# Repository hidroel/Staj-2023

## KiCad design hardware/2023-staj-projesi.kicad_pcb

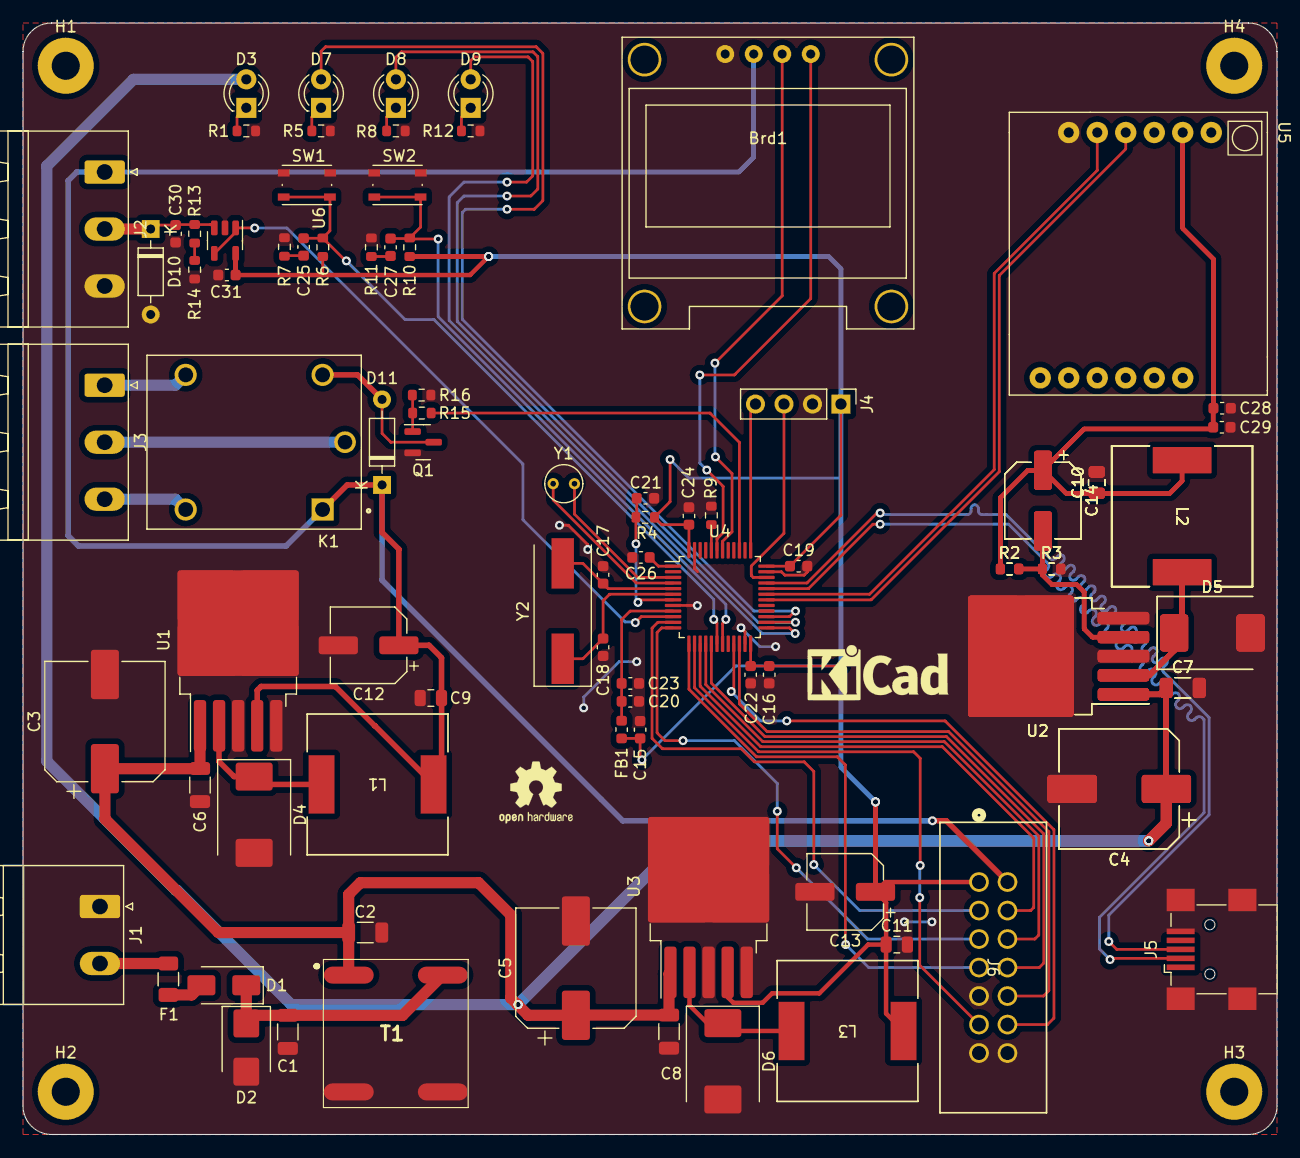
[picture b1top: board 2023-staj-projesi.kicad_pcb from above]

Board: 2 copper layers, 111.8 x 99.1 mm, 96 parts (0 on the bottom side), 57 nets.

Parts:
Brd1: SSD1306; SSD1306_0.96_Oled
C1, C2: CL31B104KBCNFNC; C_1206_3216Metric
C3, C4, C4#2, C5: 100uF/63V; CP_Elec_10x10.5
C6, C7, C7#2, C8: 470nF/100V; C_1206_3216Metric
C9, C10, C10#2, C11: 100nF/20V; C_0805_2012Metric
C12, C13, C14, C14#2: 100uF/20V; CP_Elec_6.3x7.7
C15, C20, C28: 1uF; C_0603_1608Metric
C16: 10uF; C_0603_1608Metric
C17, C18: 20pF; C_0603_1608Metric
C19, C21, C22, C24, C25, C27, C29, C31: 100nF; C_0603_1608Metric
C23, C30: 10nF; C_0603_1608Metric
C26: 1uF/10V; C_0603_1608Metric
D1: SBR3A40SAQ; D_SMA
D2: SMBJ28A; D_SMB
D3: LED_PWR; LED_D3.0mm
D4, D5, D5#2, D6: SK56; D_SMC
D7: LED_ACT; LED_D3.0mm
D8: LED_DEACT; LED_D3.0mm
D9: LED_ERR; LED_D3.0mm
D10: SMBJ28A; D_DO-35_SOD27_P7.62mm_Horizontal
D11: 1N4148; D_DO-35_SOD27_P7.62mm_Horizontal
F1: Fuse; Fuse_1206_3216Metric
FB1: 120R; L_0603_1608Metric
H1, H2, H3, H4: MountingHole; MountingHole_2.5mm_Pad
J1: POWER; PhoenixContact_MSTBA_2,5_2-G-5,08_1x02_P5.08mm_Horizontal
J2: SENSOR; PhoenixContact_MSTBA_2,5_3-G-5,08_1x03_P5.08mm_Horizontal
J3: RELAY; PhoenixContact_MSTBA_2,5_3-G-5,08_1x03_P5.08mm_Horizontal
J4: SW; PinHeader_1x04_P2.54mm_Vertical
J5: USB_B_Mini; USB_Mini-B_Wuerth_65100516121_Horizontal
J6: EXT; CONN14_1421621_WRE
K1: SRD-05VDC-SL-C; RELAY_SRD-05VDC-SL-C
L1, L2, L2#2, L3: 74477020; IND_1280-WE-PD_WRE
Q1: BC847; SOT-23
R1: 1K2; R_0603_1608Metric
R2, R2#2: 2K2; R_0603_1608Metric
R3, R3#2: 1K; R_0603_1608Metric
R4: 10K; R_0603_1608Metric
R5, R8, R12: 470R; R_0603_1608Metric
R6, R10, R15: 4K7; R_0603_1608Metric
R7, R11: 100R; R_0603_1608Metric
R9: 100K; R_0603_1608Metric
R13: 150R; R_0603_1608Metric
R14: 15R; R_0603_1608Metric
R16: 47K; R_0603_1608Metric
SW1: BTN_ACT; SW_Push_1P1T_NO_Vertical_Wuerth_434133025816
SW2: BTN_DEACT; SW_Push_1P1T_NO_Vertical_Wuerth_434133025816
T1: PA2748NL
U1: LM2596S-5; TO-263-5_TabPin3
U2, U2#2: LM2596S-ADJ; TO-263-5_TabPin3
U3: LM2596S-3.3; TO-263-5_TabPin3
U4: STM32F103C8T6; LQFP-48_7x7mm_P0.5mm
U5: SIM800L-CORE
U6: AD8603; TSOT-23-5
Y1: 32KHz; Crystal_C38-LF_D3.0mm_L8.0mm_Vertical
Y2: 8MHz; Crystal_SMD_HC49-SD

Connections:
+3.3VA: C20.1, C23.1, FB1.2, U4.9 (VDDA)
+3V3: C11.1, C13.1, C15.1, C16.1, C19.1, C22.1, C24.1, C31.1, FB1.1, J4.1, J6.1, L3.1, R4.2, R6.1, R10.1, U3.4 (FB), U4.24 (VDD), U4.36 (VDD), U4.48 (VDD), U6.5 (V+)
+3V8: C10.1, C10#2.1, C14.1, C14#2.1, C28.1, C29.1, L2.1, L2#2.1, R2.1, R2#2.1, U5.2 (VCC)
+5V: Brd1.2 (VCC), C9.1, C12.1, D11.1 (K), J2.1, J6.2, K1.A1, L1.1, U1.4 (FB)
/ADC/ADC: U4.10 (PA0), U6.1, U6.4 (-)
/ADC/SENSOR: C30.1, D10.1 (K), J2.2, R13.1, U6.3 (+)
/GSM/RXD: U4.30 (PA9), U5.4 (RXD)
/GSM/TXD: U4.31 (PA10), U5.5 (TXD)
/LCD/SCL: Brd1.3 (SCL), U4.42 (PB6)
/LCD/SDA: Brd1.4 (SDA), U4.43 (PB7)
/MCU/BOOT: R9.1, U4.44 (BOOT0)
/MCU/BTN_ACT: C25.1, R6.2, SW1.2, U4.18 (PB0)
/MCU/BTN_DEACT: C27.1, R10.2, SW2.2, U4.19 (PB1)
/MCU/I2C2_SCL: J6.12, U4.21 (PB10)
/MCU/I2C2_SDA: J6.10, U4.22 (PB11)
/MCU/LED_ACT: D7.2 (A), U4.27 (PB14)
/MCU/LED_DEACT: D8.2 (A), U4.26 (PB13)
/MCU/LED_ERR: D9.2 (A), U4.25 (PB12)
/MCU/NRST: C21.1, R4.1, U4.7 (NRST)
/MCU/PA1: J6.3, U4.11 (PA1)
/MCU/PA4: J6.11, U4.14 (PA4)
/MCU/RCC_OSC32_IN: U4.3 (PC14), Y1.2
/MCU/RCC_OSC32_OUT: U4.4 (PC15), Y1.1
/MCU/RCC_OSC_IN: C17.2, U4.5 (PD0), Y2.2
/MCU/RCC_OSC_OUT: C18.2, U4.6 (PD1), Y2.1
/MCU/RELAY: R15.1, U4.39 (PB3)
/MCU/SPI1_MISO: J6.6, U4.16 (PA6)
/MCU/SPI1_MOSI: J6.8, U4.17 (PA7)
/MCU/SPI1_SCK: J6.4, U4.15 (PA5)
/MCU/SWCLK: J4.4, U4.37 (PA14)
/MCU/SWDIO: J4.3, U4.34 (PA13)
/MCU/USART2_RX: J6.7, U4.13 (PA3)
/MCU/USART2_TX: J6.5, U4.12 (PA2)
/MCU/USB_D+: J5.3 (D+), U4.33 (PA12)
/MCU/USB_D-: J5.2 (D-), U4.32 (PA11)
/MCU/VBAT: C26.1, U4.1 (VBAT)
/Power/+12V: C2.1, C3.1, C4.1, C4#2.1, C5.1, C6.1, C7.1, C7#2.1, C8.1, D3.2 (A), T1.1 (PRI_1), U1.1 (VIN), U2.1 (VIN), U2#2.1 (VIN), U3.1 (VIN)
/Power/VCC: F1.1, J1.2
/RELAY/RLIN: J3.2, K1.COM
/RELAY/RLNC: J3.3, K1.NC
/RELAY/RLNO: J3.1, K1.NO
GND: Brd1.1 (GND), C1.2, C2.2, C3.2, C4.2, C4#2.2, C5.2, C6.2, C7.2, C7#2.2, C8.2, C9.2, C10.2, C10#2.2, C11.2, C12.2, C13.2, C15.2, C16.2, C17.1, C18.1, C19.2, C20.2, C21.2, C22.2, C23.2, C24.2, C26.2, C28.2, C29.2, C30.2, C31.2, D2.2 (A), D4.2 (A), D5.2 (A), D5#2.2 (A), D6.2 (A), D10.2 (A), J1.1, J2.3, J4.2, J5.5 (GND), J5.6 (Shield), J6.9, J6.13, J6.14, Q1.2 (E), R1.2, R3.2, R3#2.2, R5.2, R7.2, R8.2, R9.2, R11.2, R12.2, R14.2, R16.2, SW1.1, SW2.1, T1.2 (PRI_2), T1.4 (SEC_2), U1.3 (GND), U1.5 (~ON/OFF), U2.3 (GND), U2.5 (~ON/OFF), U2#2.3 (GND), U2#2.5 (~ON/OFF), U3.3 (GND), U3.5 (~ON/OFF), U4.8 (VSSA), U4.23 (VSS), U4.35 (VSS), U4.47 (VSS), U5.6 (GND), U6.2 (V-)
unnamed: C25.2, R7.1
unnamed: C27.2, R11.1
unnamed: D1.2 (A), F1.2
unnamed: C1.1, D1.1 (K), D2.1 (K), T1.3 (SEC_1)
unnamed: D3.1 (K), R1.1
unnamed: D4.1 (K), L1.2, U1.2 (OUT)
unnamed: D5.1 (K), D5#2.1 (K), L2.2, L2#2.2, U2.2 (OUT), U2#2.2 (OUT)
unnamed: D6.1 (K), L3.2, U3.2 (OUT)
unnamed: D7.1 (K), R5.1
unnamed: D8.1 (K), R8.1
unnamed: D9.1 (K), R12.1
unnamed: D11.2 (A), K1.A2, Q1.3 (C)
unnamed: Q1.1 (B), R15.2, R16.1
unnamed: R13.2, R14.1
unnamed: C14.2, C14#2.2, R2.2, R2#2.2, R3.1, R3#2.1, U2.4 (FB), U2#2.4 (FB)

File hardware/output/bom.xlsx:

Item | Qty | Reference(s) | Value | LibPart | Footprint | Datasheet | DNP | Arrow Part Number | Arrow Price/Stock | Digikey | DigikeyPN | Height | MANUFACTURER | Manufacturer_Name | Manufacturer_Part_Number | Mouser Part Number | Mouser Price/Stock | STANDARD | Sim.Device | Sim.Pins
1 | 1 | Brd1 | SSD1306 | 2023Staj:SSD1306 | 2023Staj:SSD1306_0.96_Oled
2 | 2 | C1, C2 | CL31B104KBCNFNC | Device:C_Small | Capacitor_SMD:C_1206_3216Metric | ~ |  |  |  |  | 1276-2744-2-ND
3 | 3 | C3, C4, C5 | 100uF/63V | Device:C_Polarized | Capacitor_SMD:CP_Elec_10x10.5 | ~ |  |  |  |  | 399-15648-6-ND
4 | 3 | C6, C7, C8 | 470nF/100V | Device:C_Small | Capacitor_SMD:C_1206_3216Metric | ~ |  |  |  |  | 399-C1206C474M1REC7210DKR-ND
5 | 3 | C9, C10, C11 | 100nF/20V | Device:C_Small | Capacitor_SMD:C_0805_2012Metric | ~ |  |  |  |  | 718-2500-6-ND
6 | 3 | C12, C13, C14 | 100uF/20V | Device:C_Polarized | Capacitor_SMD:CP_Elec_6.3x7.7 | ~ |  |  |  |  | 565-3210-6-ND
7 | 2 | C15, C20 | 1uF | Device:C_Small | Capacitor_SMD:C_0603_1608Metric | ~ |  |  |  |  | 311-1447-6-ND
8 | 1 | C16 | 10uF | Device:C_Small | Capacitor_SMD:C_0603_1608Metric | ~ |  |  |  |  | 13-CC0603MPX5R5BB106DKR-ND
9 | 2 | C17, C18 | 20pF | Device:C_Small | Capacitor_SMD:C_0603_1608Metric | ~ |  |  |  |  | 399-C0603C200G8HAC7867DKR-ND
10 | 6 | C19, C21, C22, C24, C25, C27 | 100nF | Device:C_Small | Capacitor_SMD:C_0603_1608Metric | ~ |  |  |  |  | AC0603KPX7R7BB104
11 | 1 | C23 | 10nF | Device:C_Small | Capacitor_SMD:C_0603_1608Metric | ~ |  |  |  |  | 13-CC0100KRX5R4BB103TR-ND
12 | 1 | C26 | 1uF/10V | Device:CP | Capacitor_SMD:C_0603_1608Metric |  |  |  |  |  | 478-12231-6-ND
13 | 1 | C28 | 1uF | Device:C | Capacitor_SMD:C_0603_1608Metric | ~
14 | 2 | C29, C31 | 100nF | Device:C | Capacitor_SMD:C_0603_1608Metric | ~
15 | 1 | C30 | 10nF | Device:C | Capacitor_SMD:C_0603_1608Metric | ~
16 | 1 | D1 | SBR3A40SAQ | Device:D | Diode_SMD:D_SMA | ~ |  |  |  |  | SBR3A40SAQ-13DITR-ND
17 | 1 | D2 | SMBJ28A | Device:D | Diode_SMD:D_SMB | ~ |  |  |  |  | SMBJ28ALFDKR-ND
18 | 1 | D3 | LED_PWR | Device:LED_Small | LED_THT:LED_D3.0mm | ~ |  |  |  |  | 1830-1004-ND
19 | 3 | D4, D5, D6 | SK56 | Device:D_Schottky | Diode_SMD:D_SMC | ~ |  |  |  |  | 1655-SK56DKR-ND
20 | 1 | D7 | LED_ACT | Device:LED_Small | LED_THT:LED_D3.0mm | ~ |  |  |  |  | 1830-1004-ND
21 | 1 | D8 | LED_DEACT | Device:LED_Small | LED_THT:LED_D3.0mm | ~ |  |  |  |  | 1830-1001-ND
22 | 1 | D9 | LED_ERR | Device:LED_Small | LED_THT:LED_D3.0mm | ~ |  |  |  |  | 1830-1000-ND
23 | 1 | D10 | SMBJ28A | Diode:1N914 | Diode_THT:D_DO-35_SOD27_P7.62mm_Horizontal | http://www.vishay.com/docs/85622/1n914.pdf |  |  |  |  |  |  |  |  |  |  |  |  | D | 1=K 2=A
24 | 1 | D11 | 1N4148 | Diode:1N4148 | Diode_THT:D_DO-35_SOD27_P7.62mm_Horizontal | https://assets.nexperia.com/documents/data-sheet/1N4148_1N4448.pdf |  |  |  |  |  |  |  |  |  |  |  |  | D | 1=K 2=A
25 | 1 | F1 | Fuse | Device:Fuse | Fuse:Fuse_1206_3216Metric | ~
26 | 1 | FB1 | 120R | Device:FerriteBead | Inductor_SMD:L_0603_1608Metric | ~ |  |  |  |  | 732-4665-6-ND
27 | 1 | J1 | POWER | Connector:Screw_Terminal_01x02 | Connector_Phoenix_MSTB:PhoenixContact_MSTBA_2,5_2-G-5,08_1x02_P5.08mm_Horizontal | ~
28 | 1 | J2 | SENSOR | Connector:Screw_Terminal_01x03 | Connector_Phoenix_MSTB:PhoenixContact_MSTBA_2,5_3-G-5,08_1x03_P5.08mm_Horizontal | ~
29 | 1 | J3 | RELAY | Connector:Screw_Terminal_01x03 | Connector_Phoenix_MSTB:PhoenixContact_MSTBA_2,5_3-G-5,08_1x03_P5.08mm_Horizontal | ~
30 | 1 | J5 | USB_B_Mini | Connector:USB_B_Mini | Connector_USB:USB_Mini-B_Wuerth_65100516121_Horizontal | ~ |  |  |  | 732-2109-2-ND
31 | 1 | J6 | EXT | Connector_Generic:Conn_02x07_Odd_Even | Connector_JAE:JAE_LY20-14P-DT1_2x07_P2.00mm_Vertical | ~
32 | 1 | K1 | SRD-05VDC-SL-C | 2023Staj:SRD-05VDC-SL-C | 2023Staj:RELAY_SRD-05VDC-SL-C |  |  |  |  |  |  |  | SONGLE RELAY |  |  |  |  | IPC-7251
33 | 3 | L1, L2, L3 | 74477020 | Damlama:74477020 | 2023Staj:IND_1280-WE-PD_WRE | 74477020 |  |  |  |  | 732-1235-6-ND
34 | 1 | Q1 | BC847 | Transistor_BJT:BC847 | Package_TO_SOT_SMD:SOT-23 | http://www.infineon.com/dgdl/Infineon-BC847SERIES_BC848SERIE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
35 | 1 | R1 | 1K2 | Device:R_Small | Resistor_SMD:R_0603_1608Metric | ~ |  |  |  |  | 13-RC0603FR-131K2LDKR-ND
36 | 1 | R2 | 2K2 | Device:R | Resistor_SMD:R_0603_1608Metric | ~
37 | 1 | R3 | 1K | Device:R | Resistor_SMD:R_0603_1608Metric | ~
38 | 1 | R4 | 10K | Device:R_Small | Resistor_SMD:R_0603_1608Metric | ~ |  |  |  |  | RNCP0603FTD10K0DKR-ND
39 | 3 | R5, R8, R12 | 470R | Device:R_Small | Resistor_SMD:R_0603_1608Metric | ~ |  |  |  |  | 1292-WR06X471JTLDKR-ND
40 | 3 | R6, R10, R15 | 4K7 | Device:R_Small | Resistor_SMD:R_0603_1608Metric | ~ |  |  |  |  | 13-RC1206FR-134K7LDKR-ND
41 | 2 | R7, R11 | 100R | Device:R_Small | Resistor_SMD:R_0603_1608Metric | ~ |  |  |  |  | RR08P100DDKR-ND
42 | 1 | R9 | 100K | Device:R | Resistor_SMD:R_0603_1608Metric | ~ |  |  |  | 311-100KHRDKR-ND
43 | 1 | R13 | 150R | Device:R | Resistor_SMD:R_0603_1608Metric | ~
44 | 1 | R14 | 15R | Device:R | Resistor_SMD:R_0603_1608Metric | ~
45 | 1 | R16 | 47K | Device:R_Small | Resistor_SMD:R_0603_1608Metric | ~
46 | 1 | SW1 | BTN_ACT | Switch:SW_Push | Button_Switch_SMD:SW_Push_1P1T_NO_Vertical_Wuerth_434133025816 | ~ |  |  |  |  | 732-13663-6-ND
47 | 1 | SW2 | BTN_DEACT | Switch:SW_Push | Button_Switch_SMD:SW_Push_1P1T_NO_Vertical_Wuerth_434133025816 | ~ |  |  |  |  | 732-13663-6-ND
48 | 1 | T1 | PA2748NL | Damlama:PA2748NL | Damlama:PA2748NL | https://productfinder.pulseelectronics.com/api/open/part-att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 |  | PA2748NL | https://www.arrow.com/en/products/pa2748nl/pulse-electronics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 |  | 553-2186-ND | 56 |  | Pulse | PA2748NL | 673-PA2748NL | https://www.mouser.co.uk/ProductDetail/Pulse-Electronics/PA2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
49 | 1 | U1 | LM2596S-5 | Regulator_Switching:LM2596S-5 | Package_TO_SOT_SMD:TO-263-5_TabPin3 | http://www.ti.com/lit/ds/symlink/lm2596.pdf |  |  |  |  | LM2596S-5.0-ND
50 | 1 | U2 | LM2596S-ADJ | Regulator_Switching:LM2596S-ADJ | Package_TO_SOT_SMD:TO-263-5_TabPin3 | http://www.ti.com/lit/ds/symlink/lm2596.pdf |  |  |  | 296-35399-2-ND
51 | 1 | U3 | LM2596S-3.3 | Regulator_Switching:LM2596S-3.3 | Package_TO_SOT_SMD:TO-263-5_TabPin3 | http://www.ti.com/lit/ds/symlink/lm2596.pdf |  |  |  |  | LM2596S-3.3/NOPB-ND
52 | 1 | U4 | STM32F103C8T6 | MCU_ST_STM32F1:STM32F103C8Tx | Package_QFP:LQFP-48_7x7mm_P0.5mm | https://www.st.com/resource/en/datasheet/stm32f103c8.pdf |  |  |  |  | 497-6063-ND
53 | 1 | U5 | SIM800L-CORE | 2023Staj:SIM800L-CORE | 2023Staj:SIM800L-CORE
54 | 1 | U6 | AD8603 | Amplifier_Operational:AD8603 | Package_TO_SOT_SMD:TSOT-23-5 | https://www.analog.com/media/en/technical-documentation/data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
55 | 1 | Y1 | 32KHz | Device:Crystal | Crystal:Crystal_C38-LF_D3.0mm_L8.0mm_Vertical | https://ecsxtal.com/store/pdf/ECS-3x8X%202x6X%201X5X.pdf |  |  |  |  | X1123-ND
56 | 1 | Y2 | 8MHz | Device:Crystal | Crystal:Crystal_SMD_HC49-SD | https://ecsxtal.com/store/pdf/ECS-3x8X%202x6X%201X5X.pdf |  |  |  |  | 631-1010-6-ND

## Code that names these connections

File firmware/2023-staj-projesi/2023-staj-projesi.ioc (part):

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Mcu.Name=STM32F103C(8-B)Tx
Mcu.Package=LQFP48
Mcu.UserName=STM32F103C8Tx
PA0-WKUP.Signal=ADCx_IN0
PA1.GPIOParameters=GPIO_Label
PA1.GPIO_Label=PA1
PA1.Signal=GPIO_Output
PA10.Mode=Asynchronous
PA10.Signal=USART1_RX
PA11.Mode=Device
PA11.Signal=USB_DM
PA12.Mode=Device
PA12.Signal=USB_DP
PA13.Mode=Serial_Wire
PA13.Signal=SYS_JTMS-SWDIO
PA14.Mode=Serial_Wire
PA14.Signal=SYS_JTCK-SWCLK
PA2.Mode=Asynchronous
PA2.Signal=USART2_TX
PA3.Mode=Asynchronous
PA3.Signal=USART2_RX
PA4.GPIOParameters=GPIO_Label
PA4.GPIO_Label=PA4
PA4.Signal=GPIO_Output
PA5.Mode=Full_Duplex_Master
PA5.Signal=SPI1_SCK
PA6.Mode=Full_Duplex_Master
PA6.Signal=SPI1_MISO
PA7.Mode=Full_Duplex_Master
PA7.Signal=SPI1_MOSI
PA9.Mode=Asynchronous
PA9.Signal=USART1_TX
PB0.GPIOParameters=GPIO_Label
PB0.GPIO_Label=BTN_ACT
PB0.Signal=GPXTI0
PB1.GPIOParameters=GPIO_Label
PB1.GPIO_Label=BTN_DEACT
PB1.Signal=GPXTI1
PB10.Mode=I2C
PB10.Signal=I2C2_SCL
PB11.Mode=I2C
PB11.Signal=I2C2_SDA
PB12.GPIOParameters=GPIO_Label
PB12.GPIO_Label=LED_ERR
PB12.Signal=GPIO_Output
PB13.GPIOParameters=GPIO_Label
PB13.GPIO_Label=LED_DEACT
PB13.Signal=GPIO_Output
PB14.GPIOParameters=GPIO_Label
PB14.GPIO_Label=LED_ACT
PB14.Signal=GPIO_Output
PB3.GPIOParameters=GPIO_Label
PB3.GPIO_Label=RELAY
PB3.Signal=GPIO_Output
PB6.GPIOParameters=GPIO_Label
PB6.GPIO_Label=LCD_SCL
PB6.Mode=I2C
PB6.Signal=I2C1_SCL
PB7.GPIOParameters=GPIO_Label
PB7.GPIO_Label=LCD_SDA
PB7.Mode=I2C
PB7.Signal=I2C1_SDA
PC14-OSC32_IN.Mode=LSE-External-Oscillator
PC14-OSC32_IN.Signal=RCC_OSC32_IN
PC15-OSC32_OUT.Mode=LSE-External-Oscillator
PC15-OSC32_OUT.Signal=RCC_OSC32_OUT
PD0-OSC_IN.Mode=HSE-External-Oscillator
PD0-OSC_IN.Signal=RCC_OSC_IN
PD1-OSC_OUT.Mode=HSE-External-Oscillator
PD1-OSC_OUT.Signal=RCC_OSC_OUT
RCC.SYSCLKFreq_VALUE=72000000
RCC.SYSCLKSource=RCC_SYSCLKSOURCE_PLLCLK
board=custom

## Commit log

2023-07-31 * 3V8 Power design fixed * Footprints assigned * Bom exported * PCB filter module placed
2023-08-05 PCB 5V power placed
2023-08-06 3.3 and 3.8 volts placed on the pcb
2023-08-08 PCB design completed
2023-08-10 Added PCB names and logos
2023-08-10 Firmware project initialized
